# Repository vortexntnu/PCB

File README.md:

# PCB Repository
This repository is for PCBs designed by members of Vortex.

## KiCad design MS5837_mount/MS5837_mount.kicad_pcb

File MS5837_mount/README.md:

# MS5837

This is a PCB designed for mounting the MS5837. It was intended to be used 
in Terrapin, but we ended up using the PCB designed by Blue Robotics.
Those files are available [here](https://github.com/bluerobotics/Bar30-Pressure-Sensor).

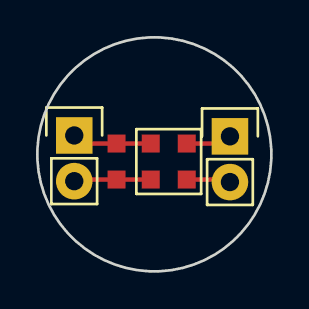
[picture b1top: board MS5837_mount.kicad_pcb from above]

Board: 2 copper layers, 13.0 x 13.0 mm, 4 parts (0 on the bottom side), 4 nets.

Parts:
C1: C; C_0805_HandSoldering
P1, P2: CONN_01X02; Pin_Header_Straight_1x02
U1: MS5837; MS5837-BA30

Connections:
GND: C1.2, P1.2, U1.1
unnamed: P2.1, U1.3
unnamed: P2.2, U1.4
VCC: C1.1, P1.1, U1.2

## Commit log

2017-01-27 Initialize mounting pcb for MS5837
2017-01-27 Complete schematic
2017-01-28 Add footprints
2017-01-28 Add pcb
2017-01-28 Add .gitignore
2017-01-28 Remove backup files
2017-04-04 Make pcb round
2017-08-31 Add readme for MS5837 board
2017-11-05 Add commit BDLib
